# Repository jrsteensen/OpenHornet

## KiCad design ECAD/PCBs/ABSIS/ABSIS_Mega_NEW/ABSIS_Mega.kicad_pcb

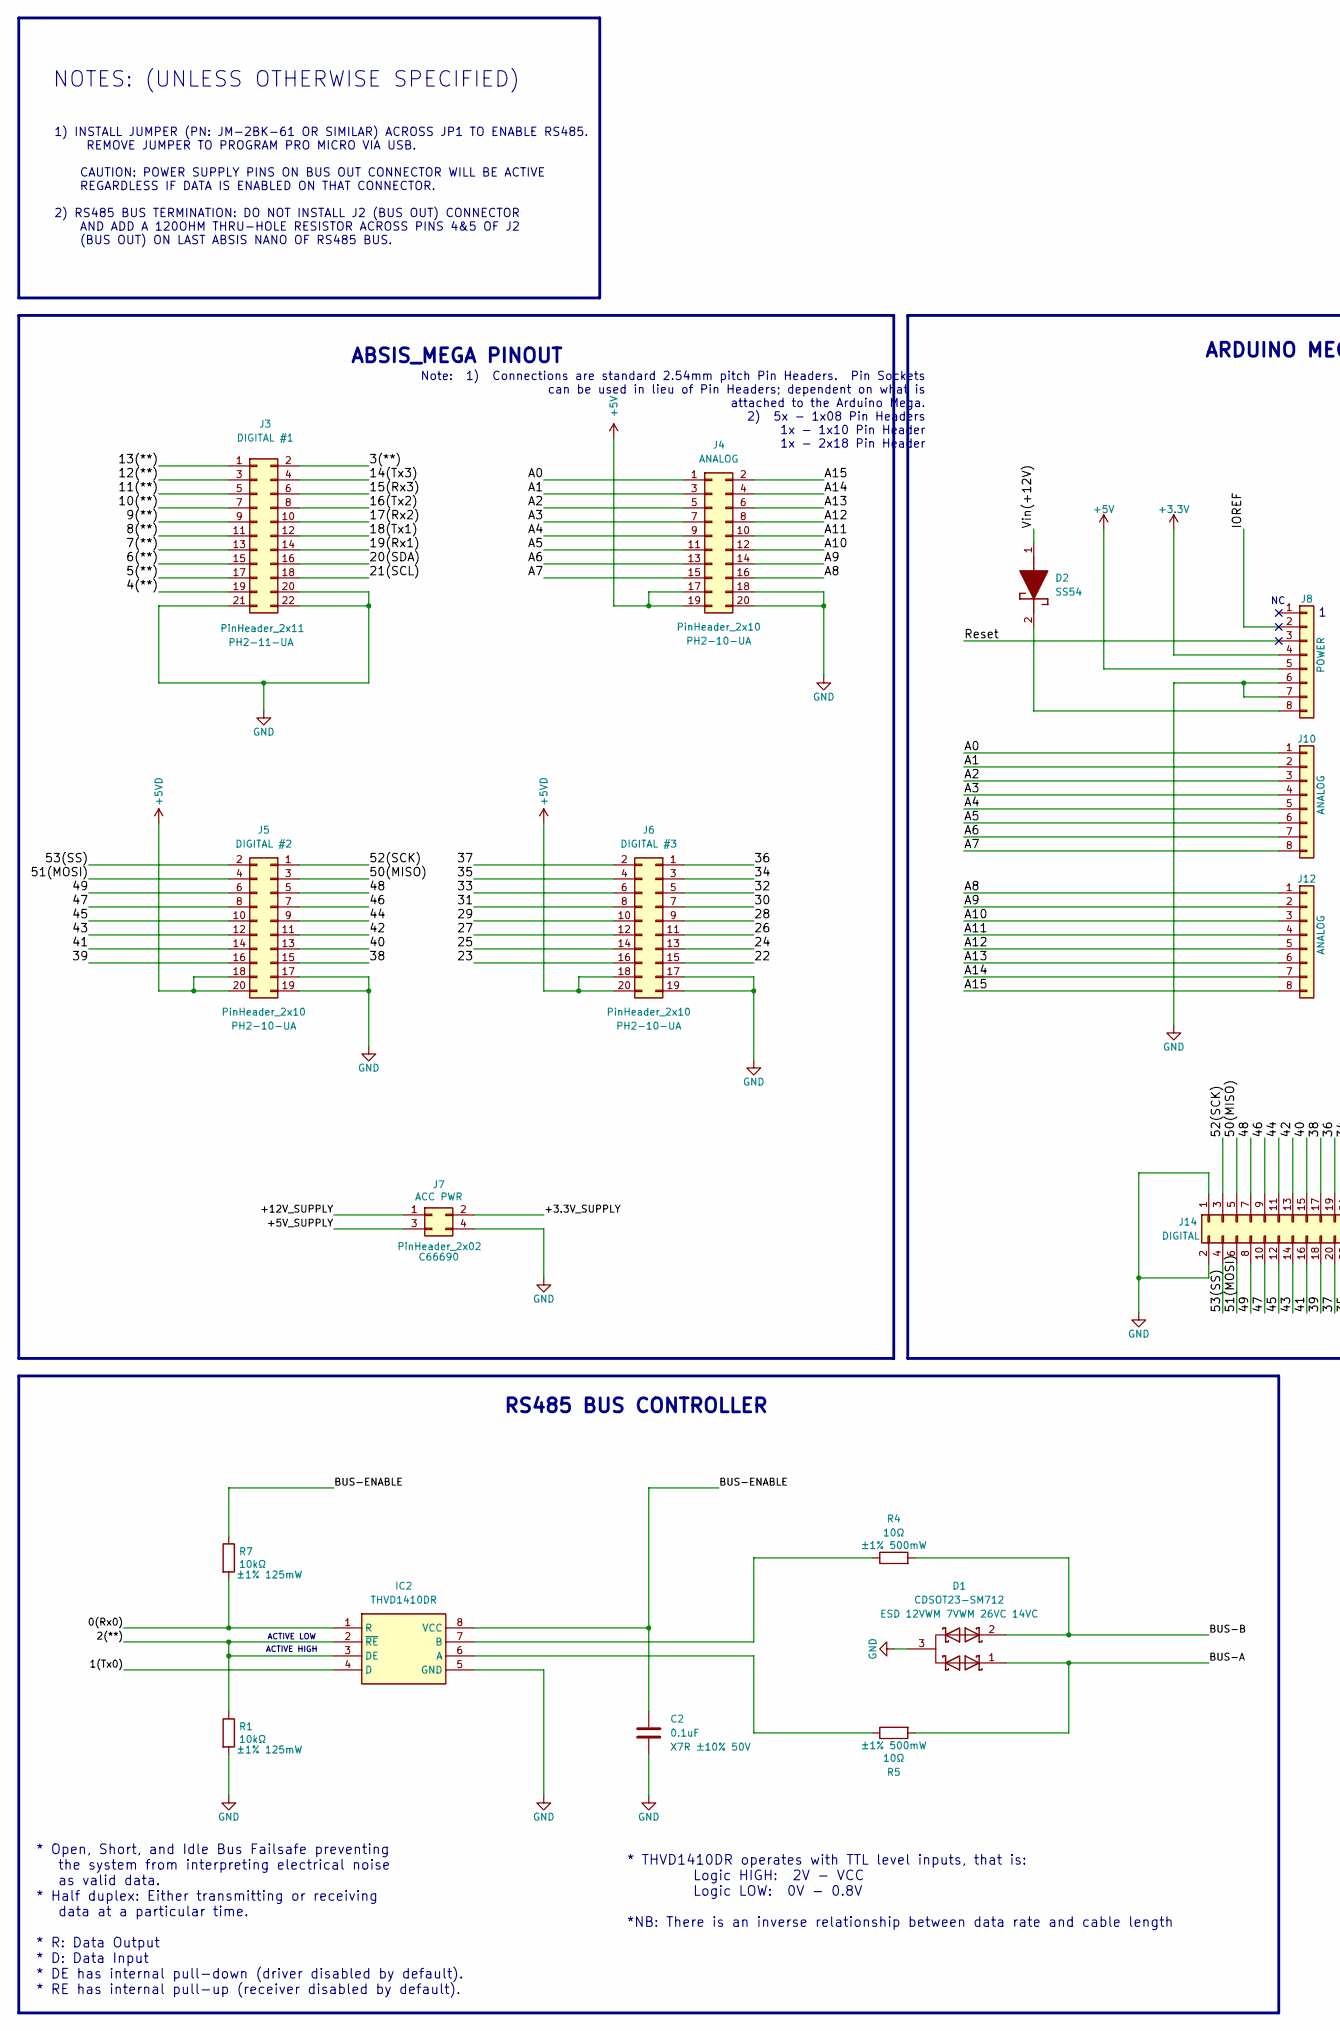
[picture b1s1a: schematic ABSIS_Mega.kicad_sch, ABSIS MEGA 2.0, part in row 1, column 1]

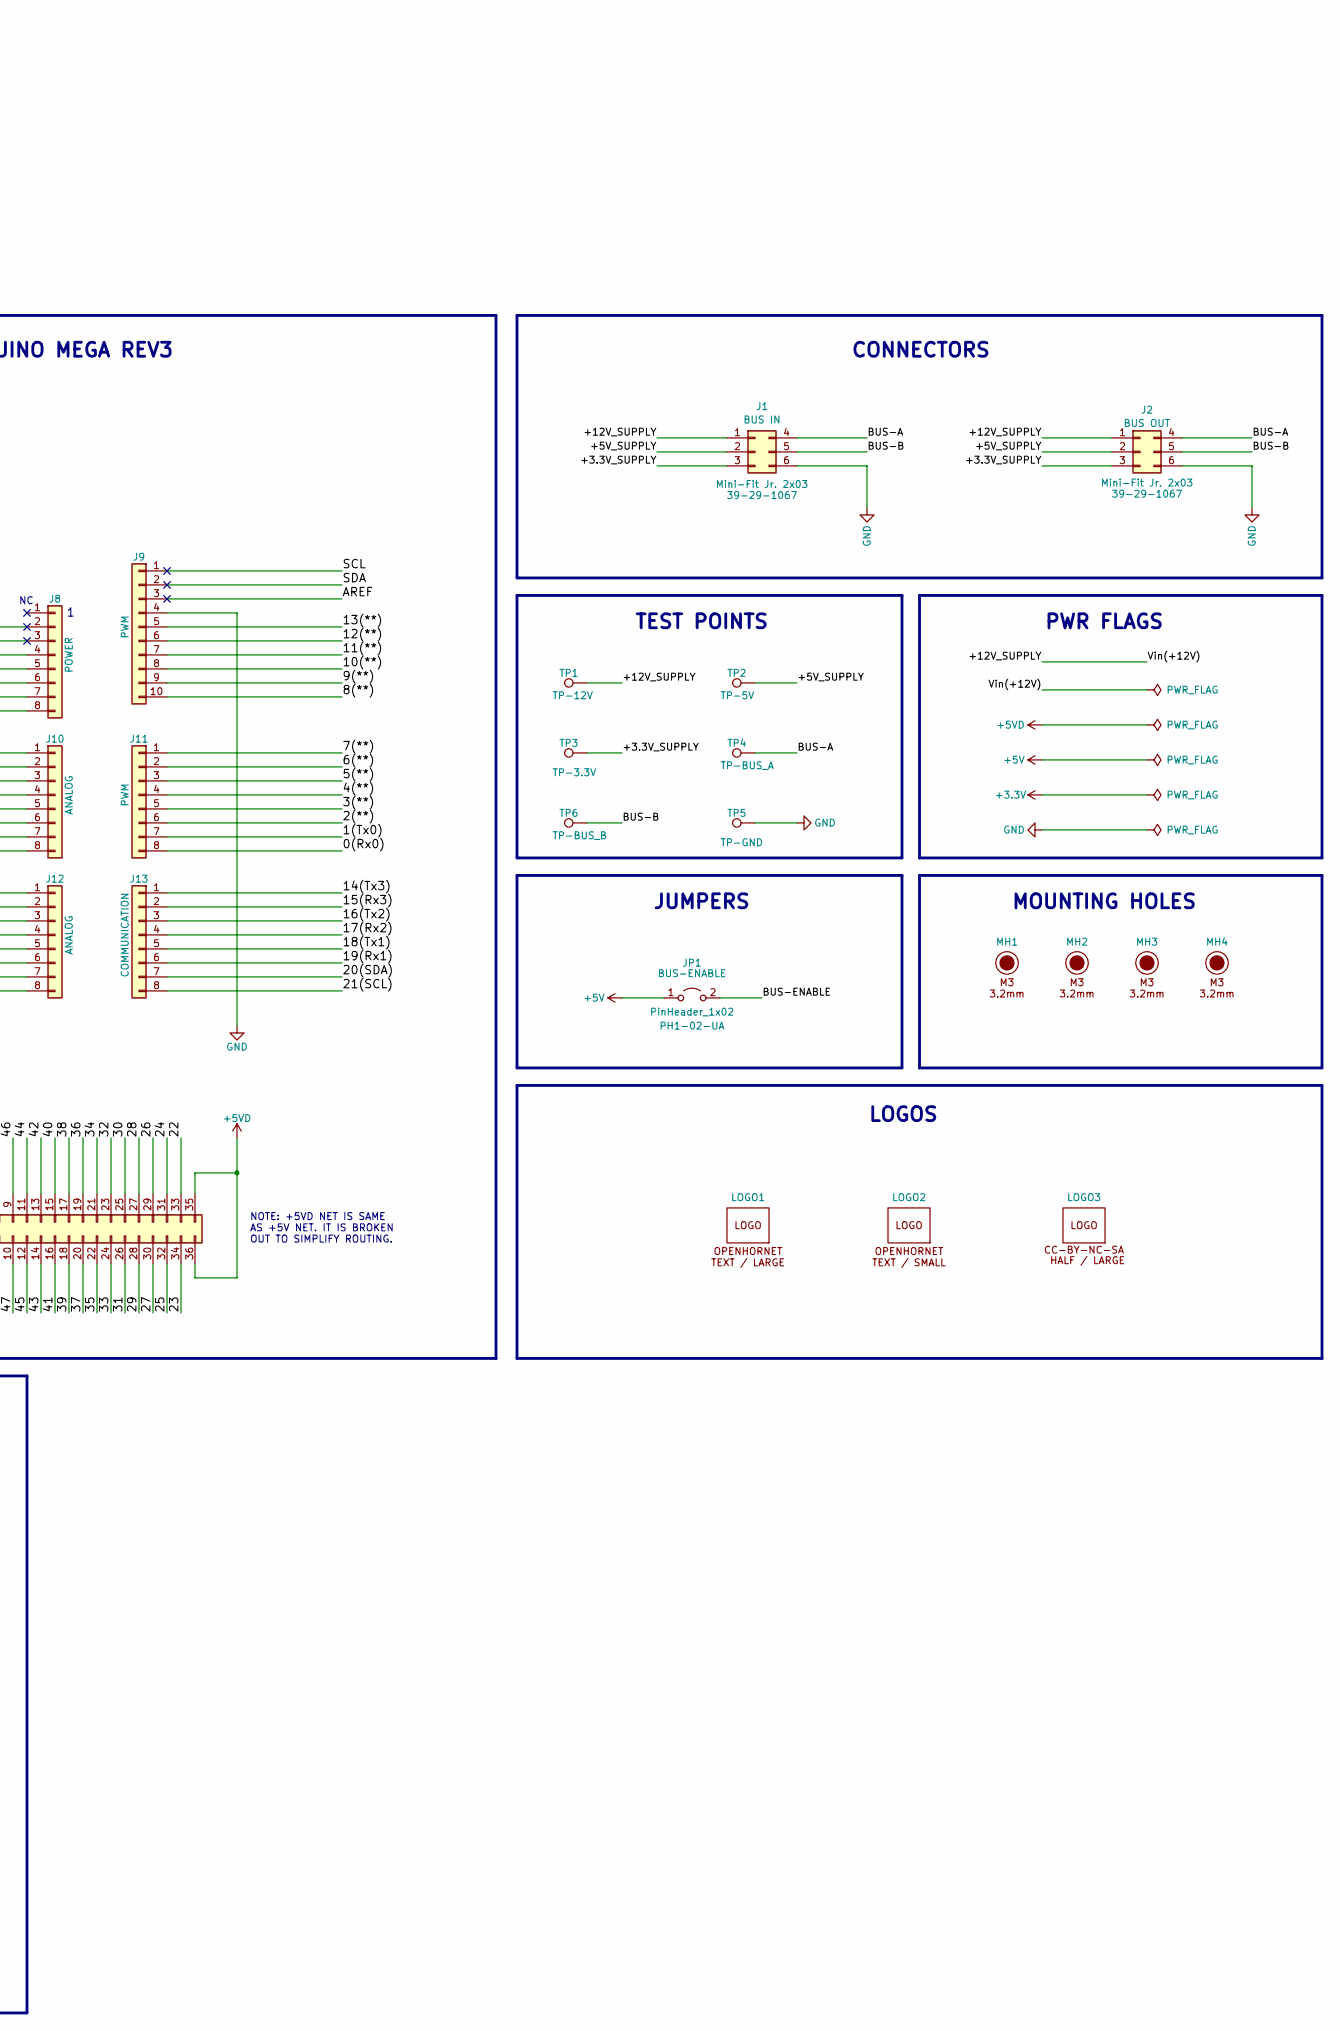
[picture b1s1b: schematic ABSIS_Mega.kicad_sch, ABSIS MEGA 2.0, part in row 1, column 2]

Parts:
C2: 0.1uF; C_0805_2012Metric; Manufacturer PN CC0805KRX7R9BB104; LCSC C49678
D1: CDSOT23-SM712; Manufacturer PN CDSOT23-SM712; LCSC C404012
D2: SS54; Manufacturer PN SS54; LCSC C22452
IC2: THVD1410DR; Manufacturer PN THVD1410DR; LCSC C2671345
J1, J2: Mini-Fit Jr. 2x03; Molex_Mini-Fit_Jr_5569-06A1_2x03_P4.20mm_Horizontal; Manufacturer PN 39-29-1067; LCSC C589019
J3: PinHeader_2x11; PinHeader_2x11_P2.54mm_Vertical; Manufacturer PN PH2-11-UA
J4, J5, J6: PinHeader_2x10; PinHeader_2x10_P2.54mm_Vertical; Manufacturer PN PH2-10-UA
J7: PinHeader_2x02; PinHeader_2x02_P2.54mm_Vertical; Manufacturer PN C66690; LCSC C66690
J8, J10, J11, J12, J13: PinHeader_1x08; PinHeader_1x08_P2.54mm_Vertical; Manufacturer PN PH1-08-UA
J9: PinHeader_1x10; PinHeader_1x10_P2.54mm_Vertical; Manufacturer PN PH1-10-UA
J14: PinHeader_2x18; PinHeader_2x18_P2.54mm_Vertical; Manufacturer PN PH2-18-UA
JP1: PinHeader_1x02; PinHeader_1x02_P2.54mm_Vertical; Manufacturer PN PH1-02-UA
LOGO1: LOGO; LOGO_OH_Text_Large
LOGO2: LOGO; LOGO_OH_Text_Small
LOGO3: LOGO; LOGO_CC-BY-NC-SA_Half_Large
MH1, MH2, MH3, MH4: M3 / 3.2mm; MountingHole_3.2mm_M3_DIN965
R1, R7: 10kΩ; R_0805_2012Metric; Manufacturer PN AC0805FR-0710KL; LCSC C140868
R4, R5: 10Ω; R_0805_2012Metric; Manufacturer PN CRCW080510R0FKEAHP; LCSC C844598
TP1, TP2, TP3, TP4, TP5, TP6: TestPoint; TestPoint_THTPad_D1.5mm_Drill0.7mm

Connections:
+3.3V: J8.4
+5V: J4.17, J4.19, J8.5, JP1.1 (A)
+5VD: J5.18, J5.20, J6.18, J6.20, J14.35, J14.36
/0(Rx0): IC2.1 (R), J11.8, R7.2
/1(Tx0): IC2.4 (D), J11.7
/2(**): IC2.2 (~RE), IC2.3 (DE), J11.6, R1.1
/3(**): J3.2, J11.5
/4(**): J3.19, J11.4
/5(**): J3.17, J11.3
/6(**): J3.15, J11.2
/7(**): J3.13, J11.1
/8(**): J3.11, J9.10
/9(**): J3.9, J9.9
/10(**): J3.7, J9.8
/11(**): J3.5, J9.7
/12(**): J3.3, J9.6
/13(**): J3.1, J9.5
/14(Tx3): J3.4, J13.1
/15(Rx3): J3.6, J13.2
/16(Tx2): J3.8, J13.3
/17(Rx2): J3.10, J13.4
/18(Tx1): J3.12, J13.5
/19(Rx1): J3.14, J13.6
/20(SDA): J3.16, J13.7
/21(SCL): J3.18, J13.8
/22: J6.15, J14.33
/23: J6.16, J14.34
/24: J6.13, J14.31
/25: J6.14, J14.32
/26: J6.11, J14.29
/27: J6.12, J14.30
/28: J6.9, J14.27
/29: J6.10, J14.28
/30: J6.7, J14.25
/31: J6.8, J14.26
/32: J6.5, J14.23
/33: J6.6, J14.24
/34: J6.3, J14.21
/35: J6.4, J14.22
/36: J6.1, J14.19
/37: J6.2, J14.20
/38: J5.15, J14.17
/39: J5.16, J14.18
/40: J5.13, J14.15
/41: J5.14, J14.16
/42: J5.11, J14.13
/43: J5.12, J14.14
/44: J5.9, J14.11
/45: J5.10, J14.12
/46: J5.7, J14.9
/47: J5.8, J14.10
/48: J5.5, J14.7
/49: J5.6, J14.8
/50(MISO): J5.3, J14.5
/51(MOSI): J5.4, J14.6
/52(SCK): J5.1, J14.3
/53(SS): J5.2, J14.4
/+3.3V_SUPPLY: J1.3, J2.3, J7.2, TP3.1
/+5V_SUPPLY: J1.2, J2.2, J7.3, TP2.1
/+12V_SUPPLY: D2.1 (A), J1.1, J2.1, J7.1, TP1.1
/A0: J4.1, J10.1
/A1: J4.3, J10.2
/A2: J4.5, J10.3
/A3: J4.7, J10.4
/A4: J4.9, J10.5
/A5: J4.11, J10.6
/A6: J4.13, J10.7
/A7: J4.15, J10.8
/A8: J4.16, J12.1
/A9: J4.14, J12.2
/A10: J4.12, J12.3
/A11: J4.10, J12.4
/A12: J4.8, J12.5
/A13: J4.6, J12.6
/A14: J4.4, J12.7
/A15: J4.2, J12.8
/AREF: J9.3
/BUS-A: D1.1, J1.4, J2.4, R5.2, TP4.1
/BUS-B: D1.2, J1.5, J2.5, R4.2, TP6.1
/BUS-ENABLE: C2.2, IC2.8 (VCC), JP1.2 (B), R7.1
/IOREF: J8.2
/Reset: J8.3
/SCL: J9.1
/SDA: J9.2
GND: C2.1, D1.3, IC2.5 (GND), J1.6, J2.6, J3.20, J3.21, J3.22, J4.18, J4.20, J5.17, J5.19, J6.17, J6.19, J7.4, J8.6, J8.7, J9.4, J14.1, J14.2, R1.2, TP5.1
unnamed: D2.2 (K), J8.8
unnamed: IC2.6 (A), R5.1
unnamed: IC2.7 (B), R4.1

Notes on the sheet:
LOGOS
* Open, Short, and Idle Bus Failsafe preventing the system from interpreting electrical noise as valid data. * Half duplex: Either transmitting or receiving data at a particular time. * R: Data Output * D: Data Input * DE has internal pull-down (driver disabled by default). * RE has internal pull-u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
RS485 BUS CONTROLLER
1) INSTALL JUMPER (PN: JM-2BK-61 OR SIMILAR) ACROSS JP1 TO ENABLE RS485. REMOVE JUMPER TO PROGRAM PRO MICRO VIA USB. CAUTION: POWER SUPPLY PINS ON BUS OUT CONNECTOR WILL BE ACTIVE REGARDLESS IF DATA IS ENABLED ON THAT CONNECTOR. 2) RS485 BUS TERMINATION: DO NOT INSTALL J2 (BUS OUT) CONNECTOR AND AD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
JUMPERS
ABSIS_MEGA PINOUT
ARDUINO MEGA REV3
NOTES: (UNLESS OTHERWISE SPECIFIED)
* THVD1410DR operates with TTL level inputs, that is: Logic HIGH: 2V - VCC Logic LOW: 0V - 0.8V *NB: There is an inverse relationship between data rate and cable length
PWR FLAGS
ACTIVE HIGH
Note: 1) Connections are standard 2.54mm pitch Pin Headers. Pin Sockets can be used in lieu of Pin Headers; dependent on what is attached to the Arduino Mega. 2) 5x - 1x08 Pin Headers 1x - 1x10 Pin Header 1x - 2x18 Pin Header
MOUNTING HOLES
TEST POINTS
ACTIVE LOW
CONNECTORS
NOTE: +5VD NET IS SAME AS +5V NET. IT IS BROKEN OUT TO SIMPLIFY ROUTING.

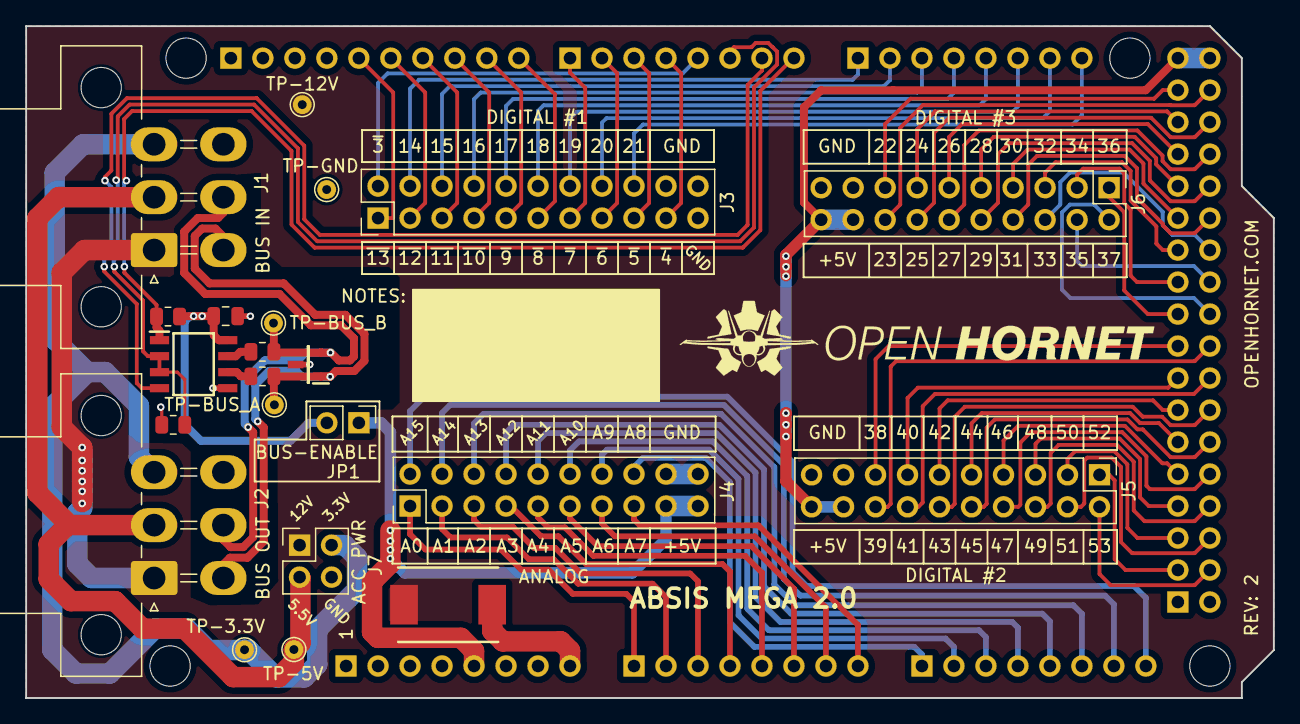
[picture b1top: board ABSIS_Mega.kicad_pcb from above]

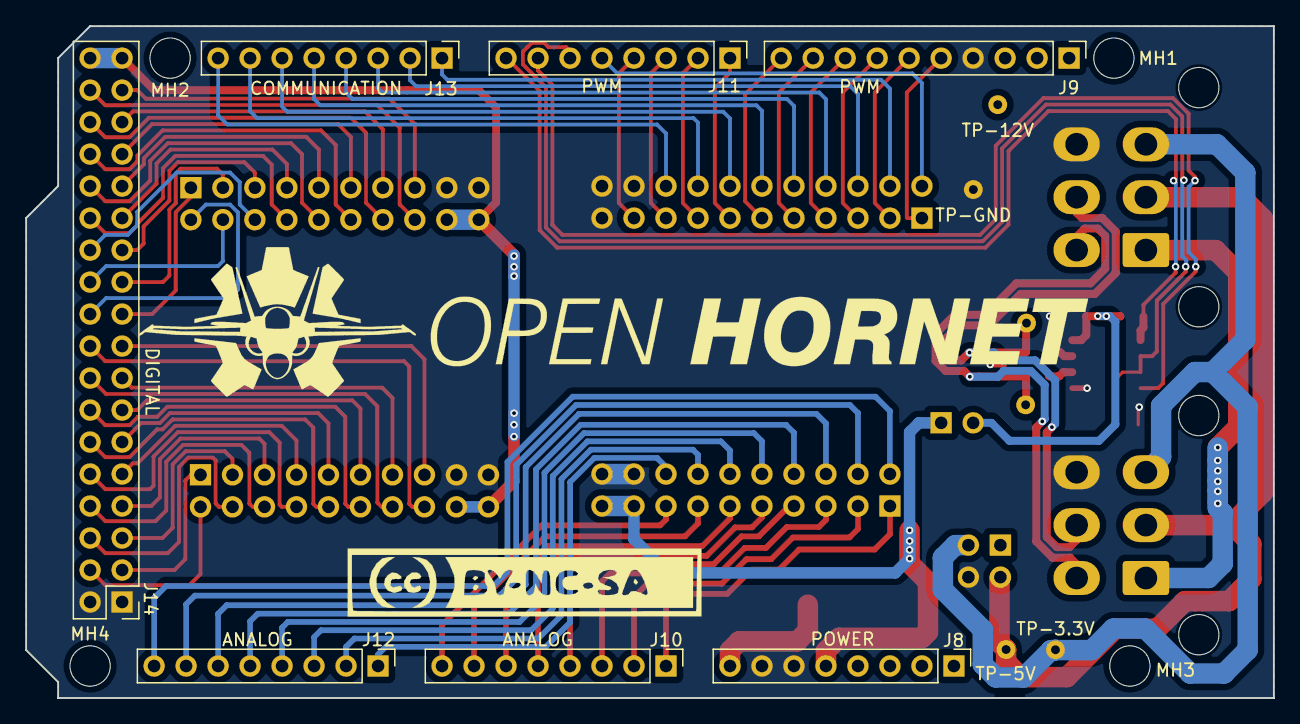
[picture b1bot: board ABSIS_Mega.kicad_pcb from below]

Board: 2 copper layers, 99.1 x 53.3 mm, 36 parts (13 on the bottom side), 82 nets.

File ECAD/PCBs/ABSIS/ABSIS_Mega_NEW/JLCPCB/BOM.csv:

"Reference","Value","Datasheet","Footprint","Qty","DNP","#","LCSC","Manufacturer PN","Notes","Description"
"C2","0.1uF","https://datasheet.lcsc.com/szlcsc/YAGEO-CChttps://datasheet.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","Capacitor_SMD:C_0805_2012Metric","1","","1","C49678","CC0805KRX7R9BB104","","X7R ±10% 50V"
"D1","CDSOT23-SM712","https://www.lcsc.com/datasheet/C404012.pdf?spm=wm.sxq.inf.gg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","CDSOT23-SM712:CDSOT23-SM712","1","","2","C404012","CDSOT23-SM712","","ESD 12VWM 7VWM 26VC 14VC"
"D2","SS54","https://datasheet.lcsc.com/szlcsc/1903042030_MDD-Jiangsu-Yut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","SS54:SS54","1","","3","C22452","SS54","","SURFACE MOUNT SCHOTTKY BARRIER RECTIFIER."
"IC2","THVD1410DR","https://www.ti.com/lit/ds/symlink/thvd1410.pdf?HQS=dis-dk-nu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","THVD1410DR:THVD1410DR","1","","4","C2671345","THVD1410DR","","3.3-V to 5-V RS-485 transceiver with +/-18-kV IEC ESD protection"
"J1,J2","Mini-Fit Jr. 2x03","https://datasheet.lcsc.com/lcsc/2005291105_MOLEX-39299062_C5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","OH_Footprints:Molex_Mini-Fit_Jr_5569-06A1_2x03_P4.20mm_Horizontal","2","","5","C589019","39-29-1067","",""
"J3","PinHeader_2x11","https://app.adam-tech.com/products/download/data_sheet/20206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","OH_Footprints:PinHeader_2x11_P2.54mm_Vertical","1","","6","","PH2-11-UA","",""
"J4,J5,J6","PinHeader_2x10","https://app.adam-tech.com/products/download/data_sheet/20206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","OH_Footprints:PinHeader_2x10_P2.54mm_Vertical","3","","7","","PH2-10-UA","",""
"J7","PinHeader_2x02","https://jlcpcb.com/partdetail/boomele_boom_Precision_elec-C6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","OH_Footprints:PinHeader_2x02_P2.54mm_Vertical","1","","8","C66690","C66690","",""
"J8,J10,J11,J12,J13","PinHeader_1x08","https://app.adam-tech.com/products/download/data_sheet/20206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","OH_Footprints:PinHeader_1x08_P2.54mm_Vertical","5","","9","","PH1-08-UA","",""
"J9","PinHeader_1x10","https://app.adam-tech.com/products/download/data_sheet/20160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","OH_Footprints:PinHeader_1x10_P2.54mm_Vertical","1","","10","","PH1-10-UA","",""
"J14","PinHeader_2x18","https://app.adam-tech.com/products/download/data_sheet/20206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","OH_Footprints:PinHeader_2x18_P2.54mm_Vertical","1","","11","","PH2-18-UA","",""
"JP1","PinHeader_1x02","https://app.adam-tech.com/products/download/data_sheet/20160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","OH_Footprints:PinHeader_1x02_P2.54mm_Vertical","1","","12","","PH1-02-UA","",""
"R1,R7","10kΩ","https://www.lcsc.com/datasheet/C140868.pdf?spm=wm.sxq.inf.gg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","Resistor_SMD:R_0805_2012Metric","2","","13","C140868","AC0805FR-0710KL","","±1% 125mW"
"R4,R5","10Ω","https://www.vishay.com/docs/20043/crcwhpe3.pdf","Resistor_SMD:R_0805_2012Metric","2","","14","C844598","CRCW080510R0FKEAHP","","±1% 500mW"

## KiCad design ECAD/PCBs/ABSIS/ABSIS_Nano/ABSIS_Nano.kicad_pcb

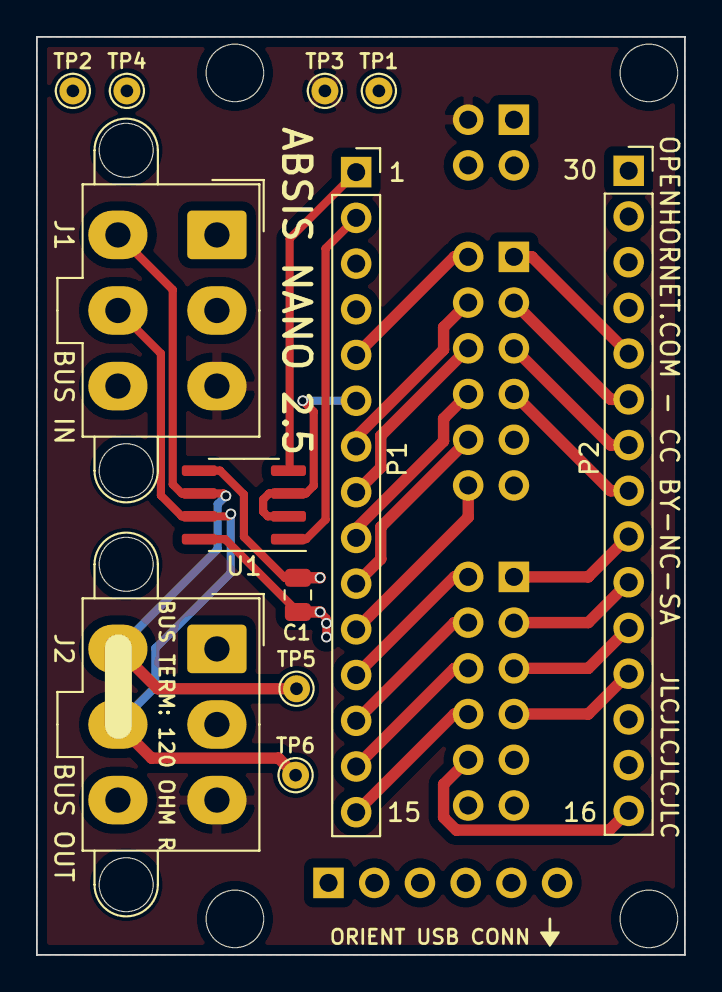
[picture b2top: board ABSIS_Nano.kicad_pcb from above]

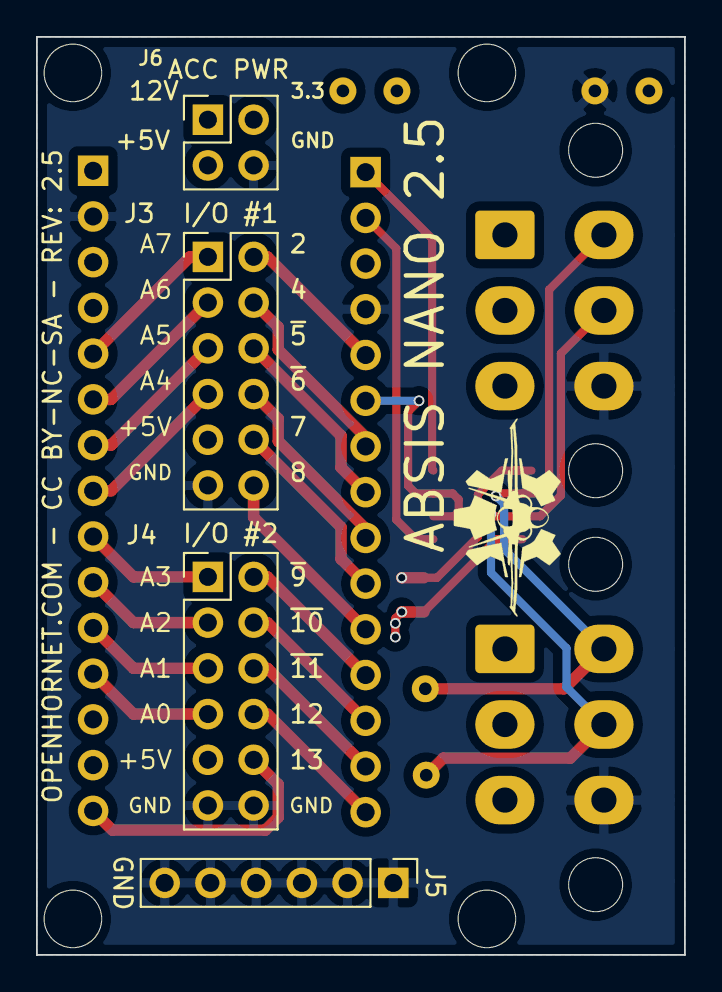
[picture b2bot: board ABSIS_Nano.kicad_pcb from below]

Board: 4 copper layers, 36.0 x 51.0 mm, 21 parts (5 on the bottom side), 29 nets.

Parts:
C1: 0.1uF; C_0805_2012Metric
H1, H2, H3, H4: MH; MountingHole_3.2mm_M3_DIN965
J1: BUS IN; Molex_Mini-Fit_Jr_5566-06A2_2x03_P4.20mm_Vertical
J2: BUS OUT; Molex_Mini-Fit_Jr_5566-06A2_2x03_P4.20mm_Vertical
J3: I/O #1; PinHeader_2x06_P2.54mm_Vertical
J4: I/O #2; PinHeader_2x06_P2.54mm_Vertical
J5: GND; PinHeader_1x06_P2.54mm_Vertical
J6: ACC PWR; PinHeader_2x02_P2.54mm_Vertical
LOGO1: OpenHornetLogoSmall; OH_LOGO_ONLY_11x6mm
P1: Digital; PinSocket_1x15_P2.54mm_Vertical
P2: Analog; PinSocket_1x15_P2.54mm_Vertical
TP1: TP-12; TestPoint_THTPad_D1.5mm_Drill0.7mm
TP2: TP-5V; TestPoint_THTPad_D1.5mm_Drill0.7mm
TP3: TP-3.3V; TestPoint_THTPad_D1.5mm_Drill0.7mm
TP4: TP-GND; TestPoint_THTPad_D1.5mm_Drill0.7mm
TP5: TP-A; TestPoint_THTPad_D1.5mm_Drill0.7mm
TP6: TP-B; TestPoint_THTPad_D1.5mm_Drill0.7mm
U1: MAX487EESA+T; SOIC-8_3.9x4.9mm_P1.27mm

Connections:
+5V: C1.1, J3.9, J4.9, P2.4, U1.8
/0(Rx): P1.2, U1.1
/1(Tx): P1.1, U1.4
/2: J3.2, P1.5
/3(**): P1.6, U1.2, U1.3
/4: J3.4, P1.7
/5(**): J3.6, P1.8
/6(**): J3.8, P1.9
/7: J3.10, P1.10
/8: J3.12, P1.11
/9(**): J4.2, P1.12
/10(**/SS): J4.4, P1.13
/11(**/MOSI): J4.6, P1.14
/12(MISO): J4.8, P1.15
/13(SCK): J4.10, P2.15
/+3.3V_SUPPLY: J1.3, J2.3, J6.2, TP3.1
/+5V_SUPPLY: J1.2, J2.2, J6.3, TP2.1
/+12V_SUPPLY: J1.1, J2.1, J6.1, P2.1, TP1.1
/A0: J4.7, P2.12
/A1: J4.5, P2.11
/A2: J4.3, P2.10
/A3: J4.1, P2.9
/A4: J3.7, P2.8
/A5: J3.5, P2.7
/A6: J3.3, P2.6
/A7: J3.1, P2.5
/BUS-A: J1.4, J2.4, TP5.1, U1.6
/BUS-B: J1.5, J2.5, TP6.1, U1.7
GND: C1.2, J1.6, J2.6, J3.11, J4.11, J4.12, J5.1, J5.2, J5.3, J5.4, J5.5, J5.6, J6.4, P1.4, P2.2, TP4.1, U1.5

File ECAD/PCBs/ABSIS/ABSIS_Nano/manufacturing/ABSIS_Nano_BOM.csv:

Comment,Designator,Footprint,LCSC
0.1uF,C1,Capacitor_SMD:C_0805_2012Metric,C49678
MH,"H1,H2,H3,H4",MountingHole:MountingHole_3.2mm_M3_DIN965,
BUS IN,J1,Connector_Molex:Molex_Mini-Fit_Jr_5566-06A2_2x03_P4.20mm_Vertical,
BUS OUT,J2,Connector_Molex:Molex_Mini-Fit_Jr_5566-06A2_2x03_P4.20mm_Vertical,
I/O #1,J3,Connector_PinHeader_2.54mm:PinHeader_2x06_P2.54mm_Vertical,MTP125-1240S1
I/O #2,J4,Connector_PinHeader_2.54mm:PinHeader_2x06_P2.54mm_Vertical,MTP125-1240S1
GND,J5,Connector_PinHeader_2.54mm:PinHeader_1x06_P2.54mm_Vertical,
ACC PWR,J6,Connector_PinHeader_2.54mm:PinHeader_2x02_P2.54mm_Vertical,MTP125-1240S1
OpenHornetLogoSmall,LOGO1,KiCAD Libraries:OH_LOGO_ONLY_11x6mm,
Digital,P1,Connector_PinSocket_2.54mm:PinSocket_1x15_P2.54mm_Vertical,
Analog,P2,Connector_PinSocket_2.54mm:PinSocket_1x15_P2.54mm_Vertical,
TP-12,TP1,TestPoint:TestPoint_THTPad_D1.5mm_Drill0.7mm,
TP-5V,TP2,TestPoint:TestPoint_THTPad_D1.5mm_Drill0.7mm,
TP-3.3V,TP3,TestPoint:TestPoint_THTPad_D1.5mm_Drill0.7mm,
TP-GND,TP4,TestPoint:TestPoint_THTPad_D1.5mm_Drill0.7mm,
TP-A,TP5,TestPoint:TestPoint_THTPad_D1.5mm_Drill0.7mm,
TP-B,TP6,TestPoint:TestPoint_THTPad_D1.5mm_Drill0.7mm,
MAX487EESA+T,U1,Package_SO:SOIC-8_3.9x4.9mm_P1.27mm,C116539

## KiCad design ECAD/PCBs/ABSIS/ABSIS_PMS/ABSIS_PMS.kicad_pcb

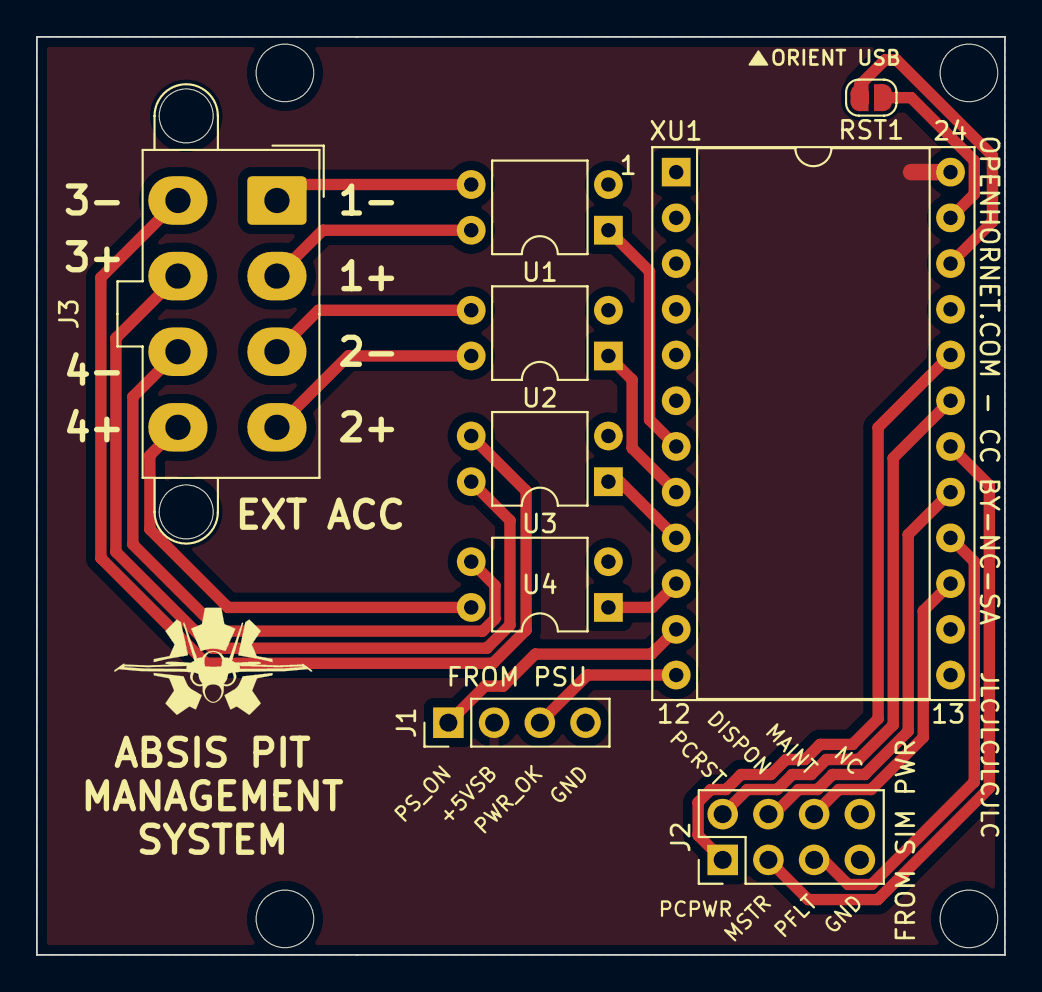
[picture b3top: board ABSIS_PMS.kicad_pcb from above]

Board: 2 copper layers, 53.8 x 51.0 mm, 15 parts (1 on the bottom side), 23 nets.

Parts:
H1, H2, H3, H4: MH; MountingHole_3.2mm_M3_DIN965
J1: FROM PSU; PinHeader_1x04_P2.54mm_Vertical
J2: FROM SIM PWR; PinHeader_2x04_P2.54mm_Vertical
J3: EXT ACC OUT; Molex_Mini-Fit_Jr_5566-08A2_2x04_P4.20mm_Vertical
LOGO1: OpenHornetLogoSmall; OH_LOGO_ONLY_11x6mm
LOGO2: OpenHornetLogoSmall; OH_LOGO_ONLY_22mm_12mm
RST1: RST; SolderJumper-2_P1.3mm_Open_RoundedPad1.0x1.5mm
U1, U2, U3, U4: 140817140010; DIP-4_W7.62mm
XU1: ProMicro_5V/16Hz; DIP-24_W15.24mm_Socket

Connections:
/+5VSB: J1.2, XU1.24
/A0: J2.4, XU1.17
/A1: J2.3, XU1.18
/A2: J2.2, XU1.19
/A3: J2.1, XU1.20
/D4_A6: U1.1, XU1.7
/D7: U4.1, XU1.10
/D8_A8: J1.1, XU1.11
/D14_MISO: J2.6, XU1.15
/D15_SCK: J2.5, XU1.16
/EXT_ACC1+: J3.2, U1.4
/EXT_ACC1-: J3.1, U1.3
/EXT_ACC2+: J3.4, U2.4
/EXT_ACC2-: J3.3, U2.3
/EXT_ACC3+: J3.6, U3.4
/EXT_ACC3-: J3.5, U3.3
/EXT_ACC4+: J3.8, U4.4
/EXT_ACC4-: J3.7, U4.3
/PWR_OK: J1.3, XU1.12
/RST: RST1.2, XU1.22
/~D5: U2.1, XU1.8
/~D6_A7: U3.1, XU1.9
GND: J1.4, J2.7, RST1.1, U1.2, U2.2, U3.2, U4.2, XU1.3, XU1.4, XU1.23

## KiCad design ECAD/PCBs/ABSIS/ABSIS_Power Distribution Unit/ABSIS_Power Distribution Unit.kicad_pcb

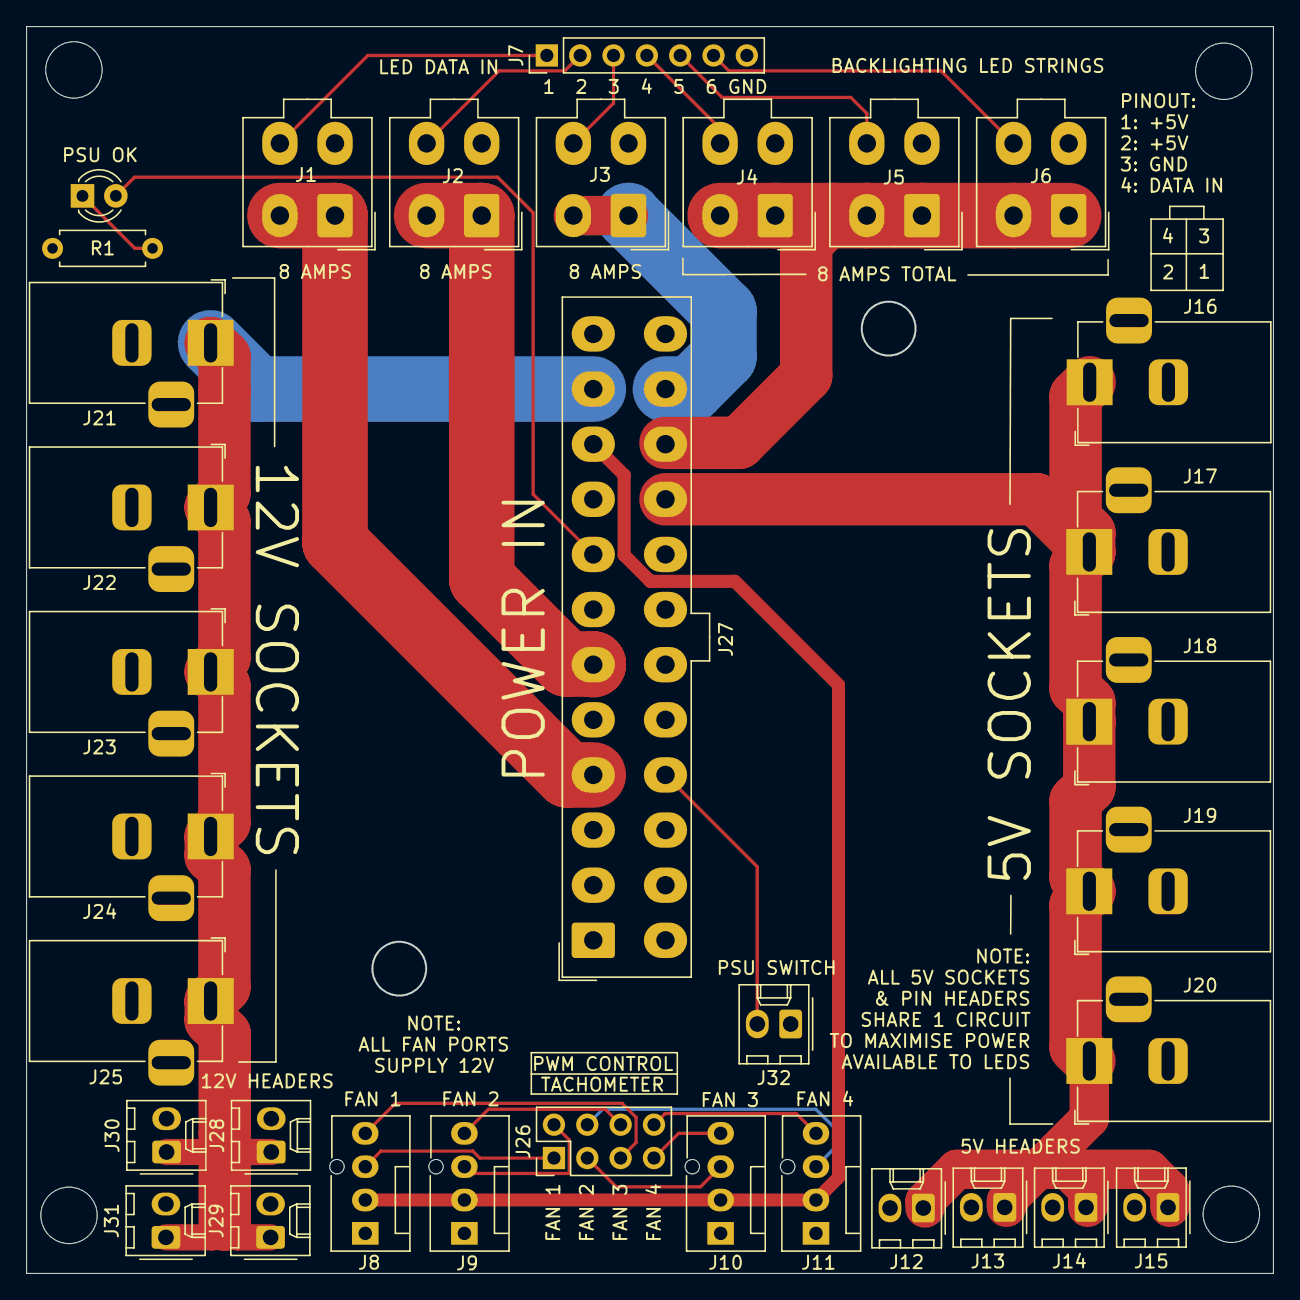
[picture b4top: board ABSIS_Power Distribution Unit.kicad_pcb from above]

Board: 2 copper layers, 95.0 x 95.0 mm, 39 parts (1 on the bottom side), 25 nets.

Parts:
1: LOGO; OH_LOGO_37.7mm_5.9mm
2, 3, 4, 5: OH_Panel_Fastner_Keepout; OH_Panel_6-32_PHS
J1, J2, J3, J4, J5, J6: Conn_01x04_Female; Molex_Mini-Fit_Jr_5566-04A_2x02_P4.20mm_Vertical
J7: Conn_01x07_Female; PinHeader_1x07_P2.54mm_Vertical
J8, J9, J10, J11: Conn_01x04_Female; FanPinHeader_1x04_P2.54mm_Vertical
J12, J13, J14, J15, J28, J29, J30, J31, J32: Conn_01x02_Female; Molex_KK-254_AE-6410-02A_1x02_P2.54mm_Vertical
J16, J17, J18, J19, J20, J21, J22, J23, J24, J25: Conn_01x02_Female; BarrelJack_Horizontal
J26: Conn_01x08_Female; PinHeader_2x04_P2.54mm_Vertical
J27: Conn_01x24_Female; Molex_Mini-Fit_Jr_5566-24A_2x12_P4.20mm_Vertical
PSU OK: LED; LED_D3.0mm
R1: R; R_Axial_DIN0207_L6.3mm_D2.5mm_P7.62mm_Horizontal

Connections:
/5VSOCKETS+: J12.1, J13.1, J14.1, J15.1, J16.1, J17.1, J18.1, J19.1, J20.1, J27.21
/12VSOCKETS+: J21.1, J22.1, J23.1, J24.1, J25.1, J27.11, J28.1, J29.1, J30.1, J31.1
/FAN+: J8.2, J9.2, J10.2, J11.2, J27.10
/LED5V1: J1.1, J1.2, J27.4
/LED5V2: J2.1, J2.2, J27.6
/LED5V3: J3.1, J3.2, J27.23
/LED5V4: J4.1, J4.2, J5.1, J5.2, J6.1, J6.2, J27.22
/LEDDATA1: J1.4, J7.1
/LEDDATA2: J2.4, J7.2
/LEDDATA3: J3.4, J7.3
/LEDDATA4: J4.4, J7.4
/LEDDATA5: J5.4, J7.5
/LEDDATA6: J6.4, J7.6
/LEDGND: J1.3, J2.3, J3.3, J4.3, J5.3, J6.3, J7.7, J8.1, J9.1, J10.1, J11.1, J12.2, J13.2, J14.2, J15.2, J16.2, J17.2, J18.2, J19.2, J20.2, J21.2, J22.2, J23.2, J24.2, J25.2, J27.3, J27.5, J27.7, J27.15, J27.17, J27.18, J27.19, J27.24, J28.2, J29.2, J30.2, J31.2, J32.1, R1.1
/PSUSW: J27.16, J32.2
/PWRGOOD: J27.8, PSU OK.2
unnamed: PSU OK.1, R1.2
unnamed: J10.3, J26.3
unnamed: J10.4, J26.7
unnamed: J11.3, J26.4
unnamed: J11.4, J26.8
unnamed: J8.3, J26.1
unnamed: J9.3, J26.2
unnamed: J8.4, J26.5
unnamed: J9.4, J26.6

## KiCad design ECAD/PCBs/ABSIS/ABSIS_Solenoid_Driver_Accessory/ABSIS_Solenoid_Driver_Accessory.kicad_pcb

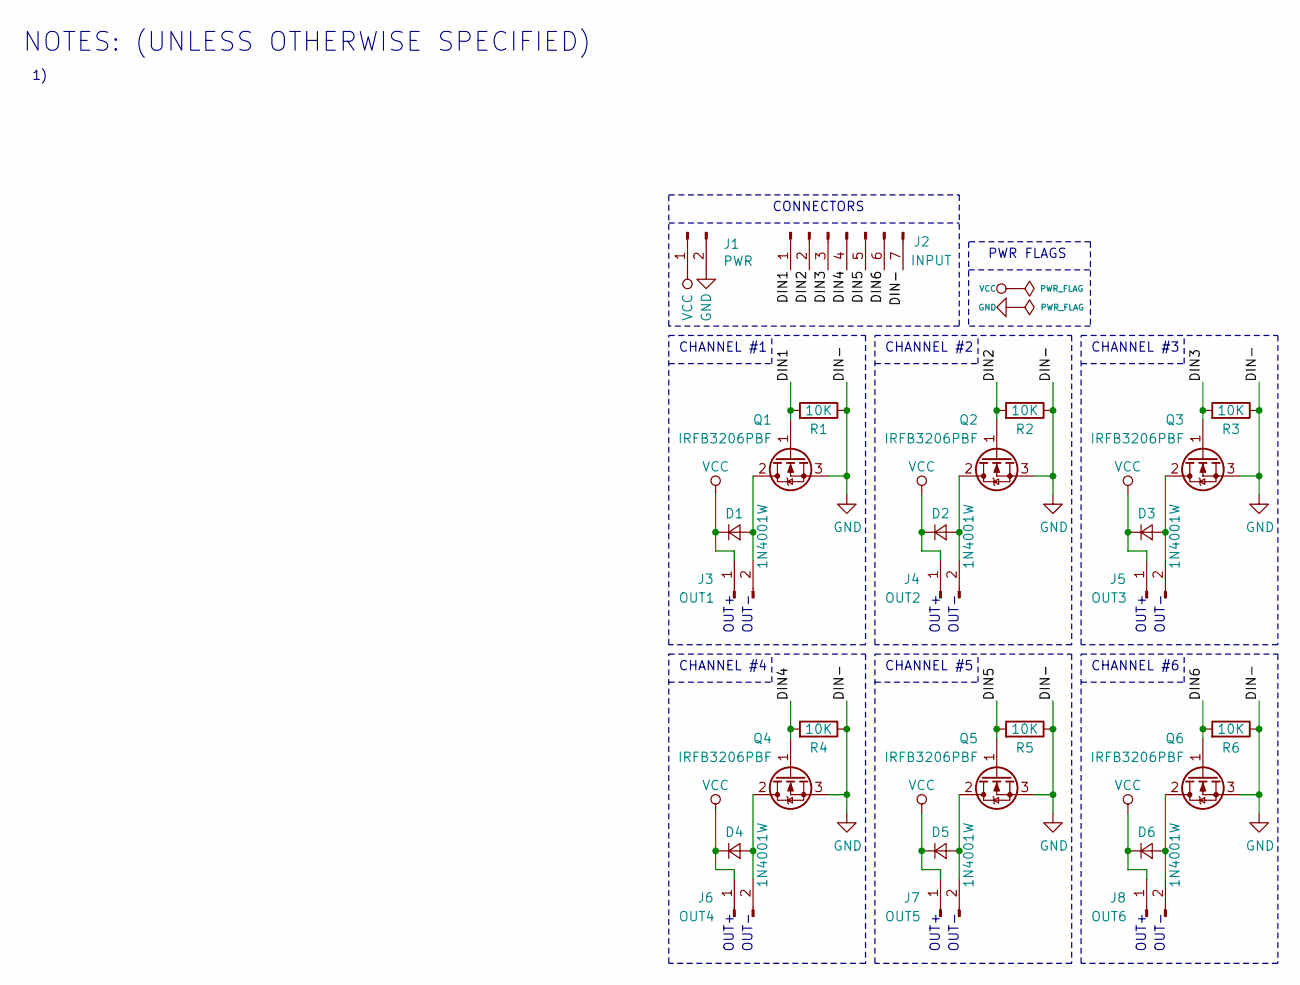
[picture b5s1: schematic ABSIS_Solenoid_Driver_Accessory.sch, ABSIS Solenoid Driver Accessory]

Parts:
D1, D2, D3, D4, D5, D6: 1N4001W; D_SOD-123; LCSC C162732
J1: PWR; PinHeader_1x02_P2.54mm_Vertical
J2: INPUT; PinHeader_1x07_P2.54mm_Vertical
J3: OUT1; PinHeader_1x02_P2.54mm_Vertical
J4: OUT2; PinHeader_1x02_P2.54mm_Vertical
J5: OUT3; PinHeader_1x02_P2.54mm_Vertical
J6: OUT4; PinHeader_1x02_P2.54mm_Vertical
J7: OUT5; PinHeader_1x02_P2.54mm_Vertical
J8: OUT6; PinHeader_1x02_P2.54mm_Vertical
Q1, Q2, Q3, Q4, Q5, Q6: IRFB3206PBF; TO-220-3_Vertical; LCSC C2642
R1, R2, R3, R4, R5, R6: 10K; R_1206_3216Metric_Pad1.42x1.75mm_HandSolder; LCSC C17902

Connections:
/DIN1: J2.1, Q1.1 (G), R1.2
/DIN2: J2.2, Q2.1 (G), R2.2
/DIN3: J2.3, Q3.1 (G), R3.2
/DIN4: J2.4, Q4.1 (G), R4.2
/DIN5: J2.5, Q5.1 (G), R5.2
/DIN6: J2.6, Q6.1 (G), R6.2
GND: J1.2, J2.7, Q1.3 (S), Q2.3 (S), Q3.3 (S), Q4.3 (S), Q5.3 (S), Q6.3 (S), R1.1, R2.1, R3.1, R4.1, R5.1, R6.1
unnamed: D1.2 (A), J3.2, Q1.2 (D)
unnamed: D2.2 (A), J4.2, Q2.2 (D)
unnamed: D3.2 (A), J5.2, Q3.2 (D)
unnamed: D4.2 (A), J6.2, Q4.2 (D)
unnamed: D5.2 (A), J7.2, Q5.2 (D)
unnamed: D6.2 (A), J8.2, Q6.2 (D)
VCC: D1.1 (K), D2.1 (K), D3.1 (K), D4.1 (K), D5.1 (K), D6.1 (K), J1.1, J3.1, J4.1, J5.1, J6.1, J7.1, J8.1

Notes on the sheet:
NOTES: (UNLESS OTHERWISE SPECIFIED)
CONNECTORS
CHANNEL #6
OUT+
OUT-
CHANNEL #5
CHANNEL #4
CHANNEL #3
CHANNEL #2
CHANNEL #1
PWR FLAGS

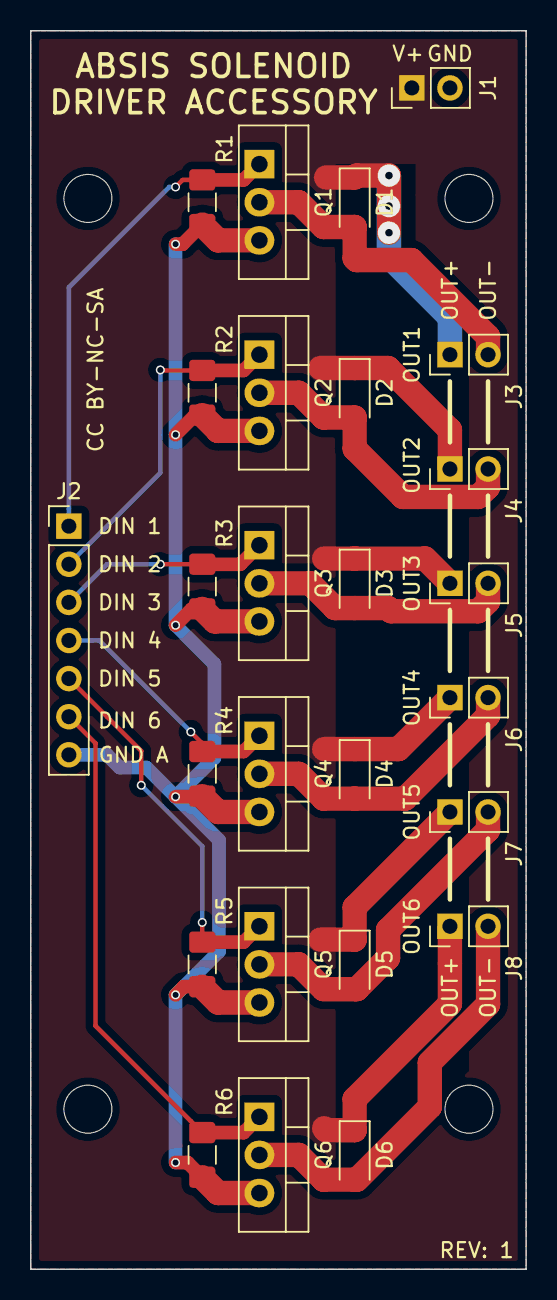
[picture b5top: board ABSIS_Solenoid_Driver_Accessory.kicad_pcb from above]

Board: 2 copper layers, 33.0 x 82.6 mm, 26 parts (0 on the bottom side), 14 nets.

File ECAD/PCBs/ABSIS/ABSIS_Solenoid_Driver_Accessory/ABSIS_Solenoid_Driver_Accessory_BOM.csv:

Reference, Quantity, Value, Footprint, Datasheet, LCSC, PN
D6 D5 D4 D3 D2 D1 ,6,1N4001W,Diode_SMD:D_SOD-123,https://datasheet.lcsc.com/szlcsc/Shandong-Jingdao-Microelec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,C162732,
J1 J3 J4 J5 J6 J7 J8,7,PWR,Connector_PinHeader_2.54mm:PinHeader_1x02_P2.54mm_Vertical,VARIOUS,,VARIOUS
J2 ,1,INPUT,Connector_PinHeader_2.54mm:PinHeader_1x07_P2.54mm_Vertical,VARIOUS,,VARIOUS
Q6 Q5 Q4 Q3 Q2 Q1 ,6,IRFB3206PBF,Package_TO_SOT_THT:TO-220-3_Vertical,https://datasheet.lcsc.com/szlcsc/1806111728_Infineon-Techno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,C2642,IRFB3206PBF
R1 R2 R3 R6 R5 R4 ,6,10K,Resistor_SMD:R_1206_3216Metric_Pad1.42x1.75mm_HandSolder,https://datasheet.lcsc.com/szlcsc/Uniroyal-Elec-1206W4F1002T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, C17902,1206W4F1002T5E

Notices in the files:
ECAD/PCBs/ABSIS/ABSIS_Mega/ABSIS_Mega.kicad_sch:
License:  CC BY-NC-SA
ECAD/PCBs/ABSIS/ABSIS_Nano/ABSIS_Nano.kicad_pcb:
OPENHORNET.COM - CC BY-NC-SA
OPENHORNET.COM - CC BY-NC-SA - REV: 2.5
ECAD/PCBs/ABSIS/ABSIS_PMS/ABSIS_PMS.kicad_pcb:
OPENHORNET.COM - CC BY-NC-SA - REV: 1
ECAD/PCBs/ABSIS/ABSIS_Power Distribution Unit/ABSIS_Power Distribution Unit.kicad_pcb:
© L. Walker 2021
ECAD/PCBs/ABSIS/ABSIS_Solenoid_Driver_Accessory/ABSIS_Solenoid_Driver_Accessory.sch:
CC BY-SA-NC
parts and their libraries:
https://creativecommons.org/licenses/by-nc-sa/4.0
